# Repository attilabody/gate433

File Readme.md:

# Shared parking space access controller

## Features

Gate433 uses cheap, standard (and insecure) gate opener remotes operating on 433 MHz to control entry and exit of vehicles allowed to acces the parking area.

Each gate opener supposed to be assigned to one vehicle and has unique code. The main purpose of it is to make unfair usage of the parking as inconvinient as possible using commodity gate opener remotes.

Features list:

* 1024 possible remote codes
* Position of each vehicle (inside, outside, unknown) is remembered. Gate opening will be denied for unexpected movements (e.g vehicle which is already inside tries to enter again)
* Access time limits by direction can be set independently for any vehicle (e.g can enter Monday to Friday from 08:30 to 17:00, can leave Monday to Friday from 08:30 to 17:30)
* Vehicle database snd device configuration stored in EEPROM
* Log stored on SD card
* Database changes can be imported from SD card
* Exceptional days (e.g. National holydays) database on SD card
* Automatic DST handling
* Simple command line interpreter on serial for database manipulation, date/time setting, log manipulation and temperature query

## Hardware

There are two versions of the hardware: Original version used Arduino Nano as central component. It is obsoleted by the newer version based on a popular STM32F103C8T6 based minimal board widely known as BluePill. It's actually cheaper on eBay or Aliexpress than the total cost of the components it contains.

Both versions ar using two inputs (usually coming from inductive loop detectors) in addition to the RF signal to decide if a vehicke intends to enter or exit. A pair of tricolor traffic lights provide feedback for drivers.

Both versions have 6 opto-isolated open drain output for 12V LED traffic lights,one opto-isolated open collector output for gate opening and two opto-isolated input for inductive loop detectors.

Second iteration have three extra features compared to the first:

* WiFi to serial bridge for wireless communication
* Rotary encoder driven simpe user interface (yet to be implemented in the firmware)
* 3D printable case modelled in FreeCAD

Prototype of STM32 based version

## Firmware

Arduino Nano based firware was built on Arduino framework using Sloeber Arduino IDE. Source files persist in folders named "gatekeeper", "common" and "libs".  
STM32 version is completely separated as it is based on STM32Cube framework. STM32 sources are placed in "gatekeeper-stm32" and "stm32goodies" folder.

## Schematics and PCB

Arduino based first version hardware developed using proprietrary Eagle free version, and obsoleted by STM32 version but schematics of the [mainboard](docs/V1_mainboard.pdf) and the [IO panel](docs/V1_extio.pdf) are still available for reference.

As mentioned above, hardware of STM32 version designed using KiCAD. The complete EDA project is available in the hardware/STM32 folder. Here are the [schematics](docs/bluepill.pdf) in PDF for easier access.

PCB design for STM32 bsed version

Assembled STM32 panel with modules installed

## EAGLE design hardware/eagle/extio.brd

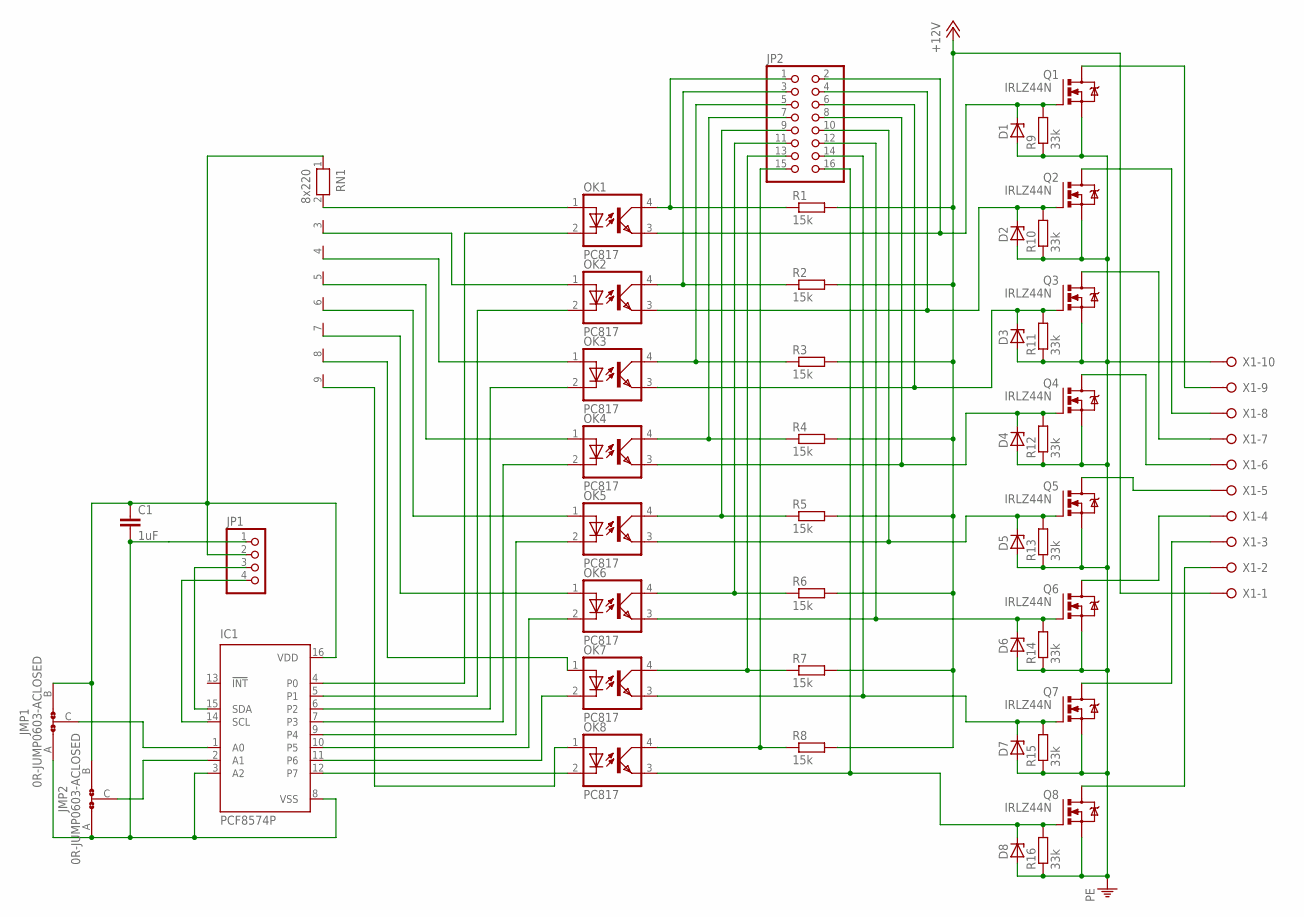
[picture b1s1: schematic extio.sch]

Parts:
C1: 1uF; C0603
D1, D2, D3, D4, D5, D6, D7, D8: ZENER-DIODESOD80C; SOD80C
IC1: PCF8574P; DIL16
JMP1, JMP2: 0R-JUMP0603-ACLOSED; JMP0603-ACLOSED
JP1: PINHD-1X4; 1X04
JP2: PINHD-2X8; 2X08
OK1, OK2, OK3, OK4, OK5, OK6, OK7, OK8: PC817; DIL04
Q1, Q2, Q3, Q4, Q5, Q6, Q7, Q8: IRLZ44N; TO220V
R1, R2, R3, R4, R5, R6, R7, R8: 15k; R0603
R9, R10, R11, R12, R13, R14, R15, R16: 33k; R0603
RN1: 8x220; RN-9
X1: W237-10P

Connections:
+12V: R1.2, R2.2, R3.2, R4.2, R5.2, R6.2, R7.2, R8.2, X1.1
GND: C1.2, IC1.3 (A2), IC1.8 (VSS), JMP1.A, JMP2.A, JP1.1
unnamed: IC1.1 (A0), JMP1.C
unnamed: IC1.2 (A1), JMP2.C
unnamed: OK1.1 (A), RN1.2
unnamed: Q1.2 (D), X1.9
unnamed: JP2.1, OK1.4 (COL), R1.1
unnamed: JP2.3, OK2.4 (COL), R2.1
unnamed: JP2.5, OK3.4 (COL), R3.1
unnamed: JP2.7, OK4.4 (COL), R4.1
unnamed: JP2.9, OK5.4 (COL), R5.1
unnamed: JP2.11, OK6.4 (COL), R6.1
unnamed: JP2.13, OK7.4 (COL), R7.1
unnamed: IC1.12 (P7), OK8.2 (C)
unnamed: IC1.11 (P6), OK7.2 (C)
unnamed: IC1.10 (P5), OK6.2 (C)
unnamed: IC1.9 (P4), OK5.2 (C)
unnamed: IC1.7 (P3), OK4.2 (C)
unnamed: IC1.6 (P2), OK3.2 (C)
unnamed: IC1.5 (P1), OK2.2 (C)
unnamed: IC1.4 (P0), OK1.2 (C)
unnamed: OK2.1 (A), RN1.3
unnamed: OK3.1 (A), RN1.4
unnamed: OK4.1 (A), RN1.5
unnamed: OK5.1 (A), RN1.6
unnamed: OK6.1 (A), RN1.7
unnamed: OK7.1 (A), RN1.8
unnamed: OK8.1 (A), RN1.9
unnamed: D1.C, JP2.2, OK1.3 (EMIT), Q1.1 (G), R9.2
unnamed: IC1.15 (SDA), JP1.3
unnamed: JP2.15, OK8.4 (COL), R8.1
unnamed: D2.C, JP2.4, OK2.3 (EMIT), Q2.1 (G), R10.2
unnamed: D3.C, JP2.6, OK3.3 (EMIT), Q3.1 (G), R11.2
unnamed: D4.C, JP2.8, OK4.3 (EMIT), Q4.1 (G), R12.2
unnamed: D5.C, JP2.10, OK5.3 (EMIT), Q5.1 (G), R13.2
unnamed: D6.C, JP2.12, OK6.3 (EMIT), Q6.1 (G), R14.2
unnamed: IC1.14 (SCL), JP1.4
unnamed: D7.C, JP2.14, OK7.3 (EMIT), Q7.1 (G), R15.2
unnamed: D8.C, JP2.16, OK8.3 (EMIT), Q8.1 (G), R16.2
unnamed: Q2.2 (D), X1.8
unnamed: C1.1, IC1.16 (VDD), JMP1.B, JMP2.B, JP1.2, RN1.1
unnamed: Q3.2 (D), X1.7
unnamed: Q4.2 (D), X1.6
unnamed: Q5.2 (D), X1.5
unnamed: Q6.2 (D), X1.4
unnamed: Q7.2 (D), X1.3
unnamed: Q8.2 (D), X1.2
PE: D1.A, D2.A, D3.A, D4.A, D5.A, D6.A, D7.A, D8.A, Q1.3 (S), Q2.3 (S), Q3.3 (S), Q4.3 (S), Q5.3 (S), Q6.3 (S), Q7.3 (S), Q8.3 (S), R9.1, R10.1, R11.1, R12.1, R13.1, R14.1, R15.1, R16.1, X1.10

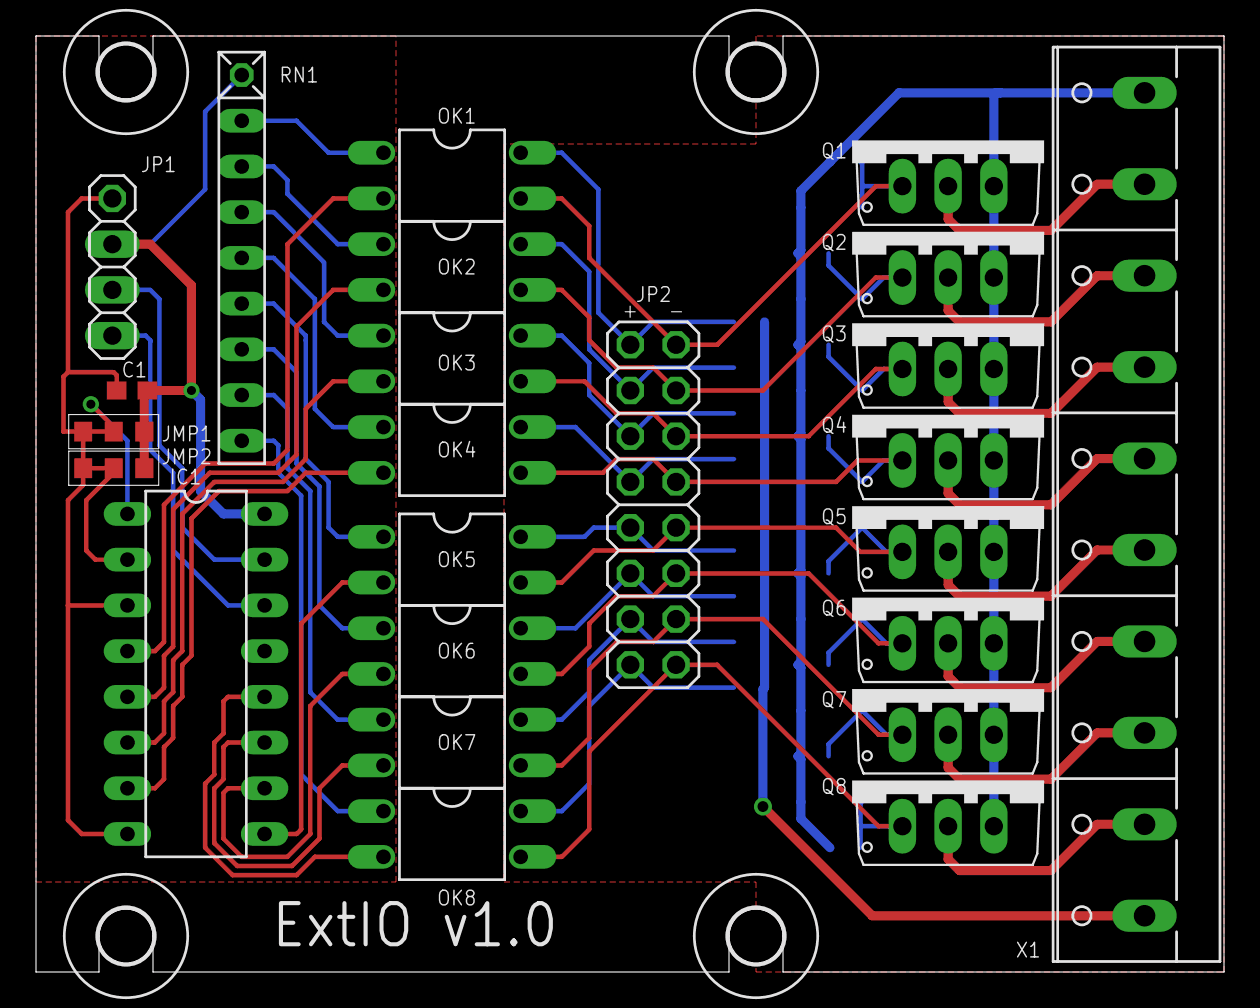
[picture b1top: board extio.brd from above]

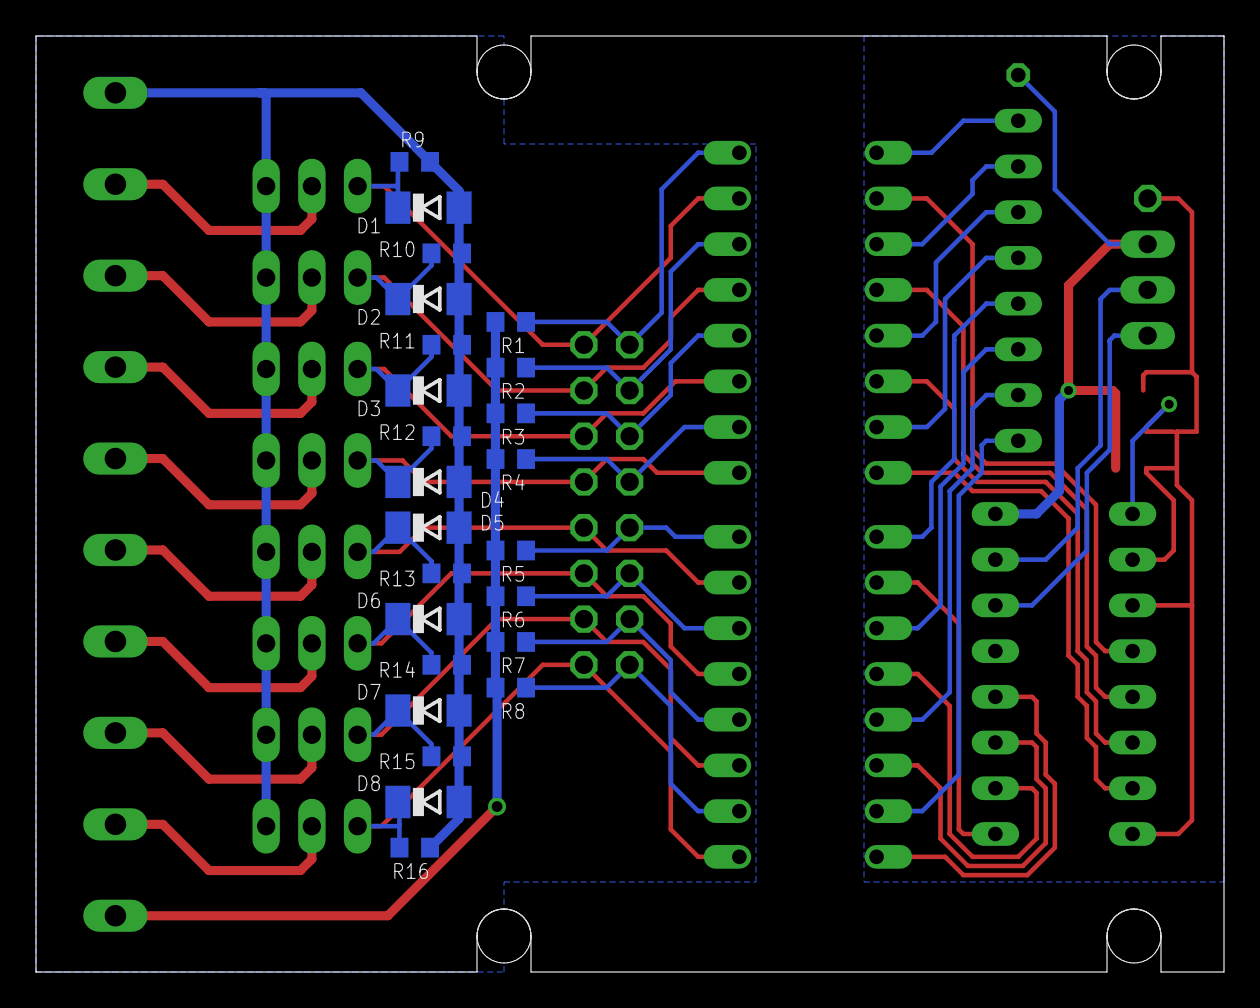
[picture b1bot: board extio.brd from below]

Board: 2 copper layers, 66.0 x 52.0 mm, 52 parts (24 on the bottom side), 48 nets.

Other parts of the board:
U$1, U$2, U$3, U$4: 3,0

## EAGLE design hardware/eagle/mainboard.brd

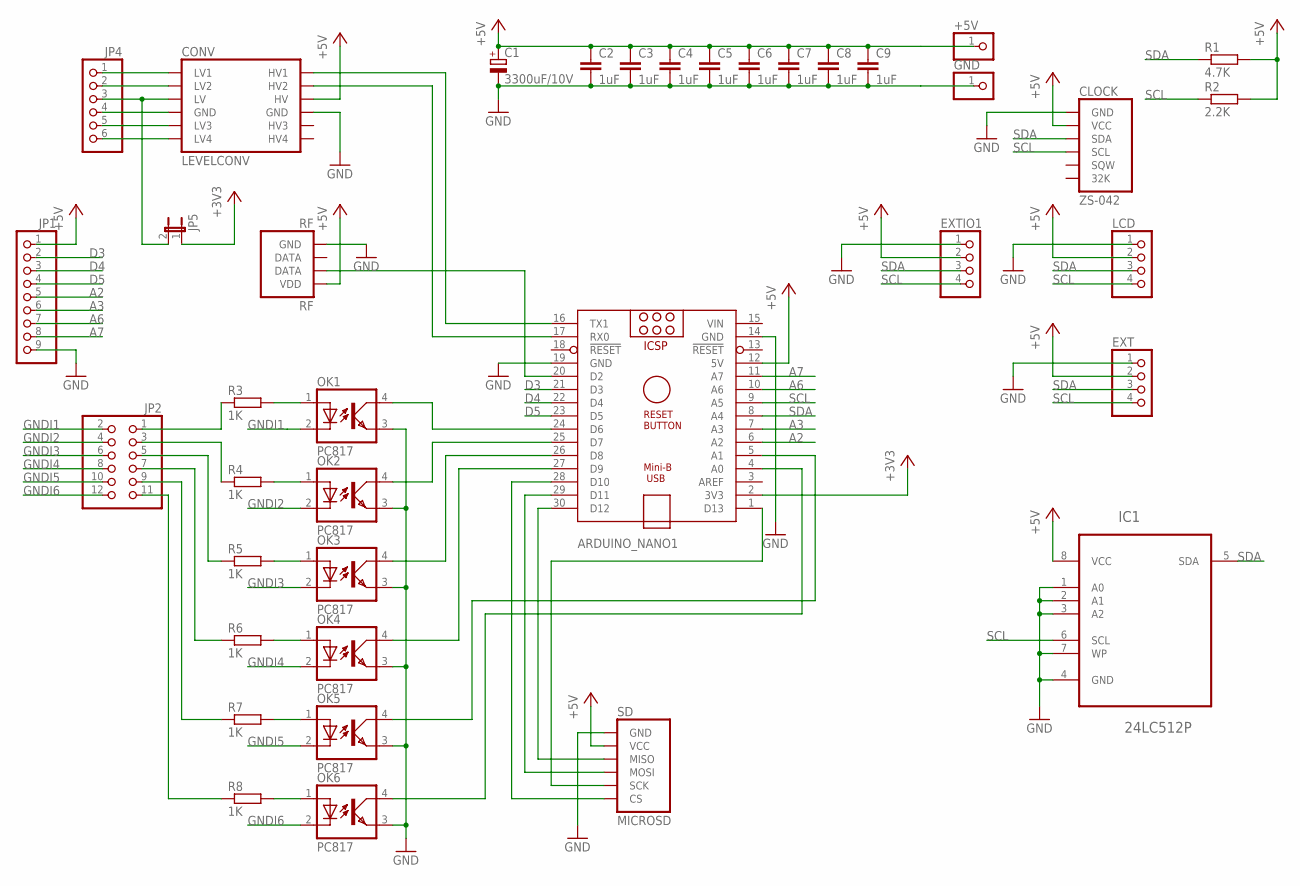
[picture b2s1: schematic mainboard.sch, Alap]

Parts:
+5V: PINHD-1X1; 1X01
ARDUINO_NANO1: ARDUINO_NANO
C1: 3300uF/10V; E5-10,5
C2, C3, C4, C5, C6, C7, C8, C9: 1uF; C0603
CLOCK: ZS-042
CONV: LEVELCONV
EXT: PINHD-1X4; 1X04
EXTIO1: PINHD-1X4; 1X04
GND: PINHD-1X1; 1X01
IC1: 24LC512P; DIP254P762X533-8
JP1: PINHD-1X9; 1X09
JP2: PINHD-2X6; 2X06
JP4: PINHD-1X6; 1X06
JP5: JP1E; JP1
LCD: PINHD-1X4; 1X04
OK1, OK2, OK3, OK4, OK5, OK6: PC817; DIL04
R1: 4.7K; R0603
R2: 2.2K; R0603
R3, R4, R5, R6, R7, R8: 1K; R0603
RF: RF
SD: MICROSD

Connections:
+3V3: ARDUINO_NANO1.2 (3V3), JP5.1
+5V: +5V.1, ARDUINO_NANO1.12 (5V), C1.+, C2.1, C3.1, C4.1, C5.1, C6.1, C7.1, C8.1, C9.1, CLOCK.2 (VCC), CONV.10 (HV), EXT.2, EXTIO1.2, IC1.8 (VCC), JP1.1, LCD.2, R1.2, R2.2, RF.4 (VDD), SD.2 (VCC)
A2: ARDUINO_NANO1.6 (A2), JP1.5
A3: ARDUINO_NANO1.7 (A3), JP1.6
A6: ARDUINO_NANO1.10 (A6), JP1.7
A7: ARDUINO_NANO1.11 (A7), JP1.8
D3: ARDUINO_NANO1.21 (D3), JP1.2
D4: ARDUINO_NANO1.22 (D4), JP1.3
D5: ARDUINO_NANO1.23 (D5), JP1.4
GND: ARDUINO_NANO1.14 (GND), ARDUINO_NANO1.19 (GND), C1.-, C2.2, C3.2, C4.2, C5.2, C6.2, C7.2, C8.2, C9.2, CLOCK.1 (GND), CONV.9 (GND), EXT.1, EXTIO1.1, GND.1, IC1.1 (A0), IC1.2 (A1), IC1.3 (A2), IC1.4 (GND), IC1.7 (WP), JP1.9, LCD.1, OK1.3 (EMIT), OK2.3 (EMIT), OK3.3 (EMIT), OK4.3 (EMIT), OK5.3 (EMIT), OK6.3 (EMIT), RF.1 (GND), SD.1 (GND)
GNDI1: JP2.2, OK1.2 (C)
GNDI2: JP2.4, OK2.2 (C)
GNDI3: JP2.6, OK3.2 (C)
GNDI4: JP2.8, OK4.2 (C)
GNDI5: JP2.10, OK5.2 (C)
GNDI6: JP2.12, OK6.2 (C)
unnamed: CONV.1 (LV1), JP4.1
unnamed: JP2.11, R8.1
unnamed: OK1.1 (A), R3.2
unnamed: ARDUINO_NANO1.27 (D9), OK4.4 (COL)
unnamed: ARDUINO_NANO1.26 (D8), OK3.4 (COL)
unnamed: ARDUINO_NANO1.25 (D7), OK2.4 (COL)
unnamed: JP2.9, R7.1
unnamed: CONV.2 (LV2), JP4.2
unnamed: CONV.3 (LV), JP4.3, JP5.2
unnamed: CONV.5 (LV3), JP4.5
unnamed: CONV.6 (LV4), JP4.6
unnamed: CONV.4 (GND), JP4.4
unnamed: ARDUINO_NANO1.28 (D10), SD.6 (CS)
unnamed: ARDUINO_NANO1.1 (D13), SD.5 (SCK)
unnamed: ARDUINO_NANO1.29 (D11), SD.4 (MOSI)
unnamed: ARDUINO_NANO1.30 (D12), SD.3 (MISO)
unnamed: ARDUINO_NANO1.24 (D6), OK1.4 (COL)
unnamed: JP2.1, R3.1
unnamed: JP2.3, R4.1
unnamed: ARDUINO_NANO1.4 (A0), OK6.4 (COL)
unnamed: ARDUINO_NANO1.5 (A1), OK5.4 (COL)
unnamed: ARDUINO_NANO1.20 (D2), RF.3 (DATA)
unnamed: JP2.5, R5.1
unnamed: JP2.7, R6.1
unnamed: OK2.1 (A), R4.2
unnamed: OK3.1 (A), R5.2
unnamed: OK4.1 (A), R6.2
unnamed: OK5.1 (A), R7.2
unnamed: OK6.1 (A), R8.2
unnamed: ARDUINO_NANO1.16 (TX1), CONV.12 (HV1)
unnamed: ARDUINO_NANO1.17 (RX0), CONV.11 (HV2)
SCL: ARDUINO_NANO1.9 (A5), CLOCK.4 (SCL), EXT.4, EXTIO1.4, IC1.6 (SCL), LCD.4, R2.1
SDA: ARDUINO_NANO1.8 (A4), CLOCK.3 (SDA), EXT.3, EXTIO1.3, IC1.5 (SDA), LCD.3, R1.1
VIN: ARDUINO_NANO1.15 (VIN)

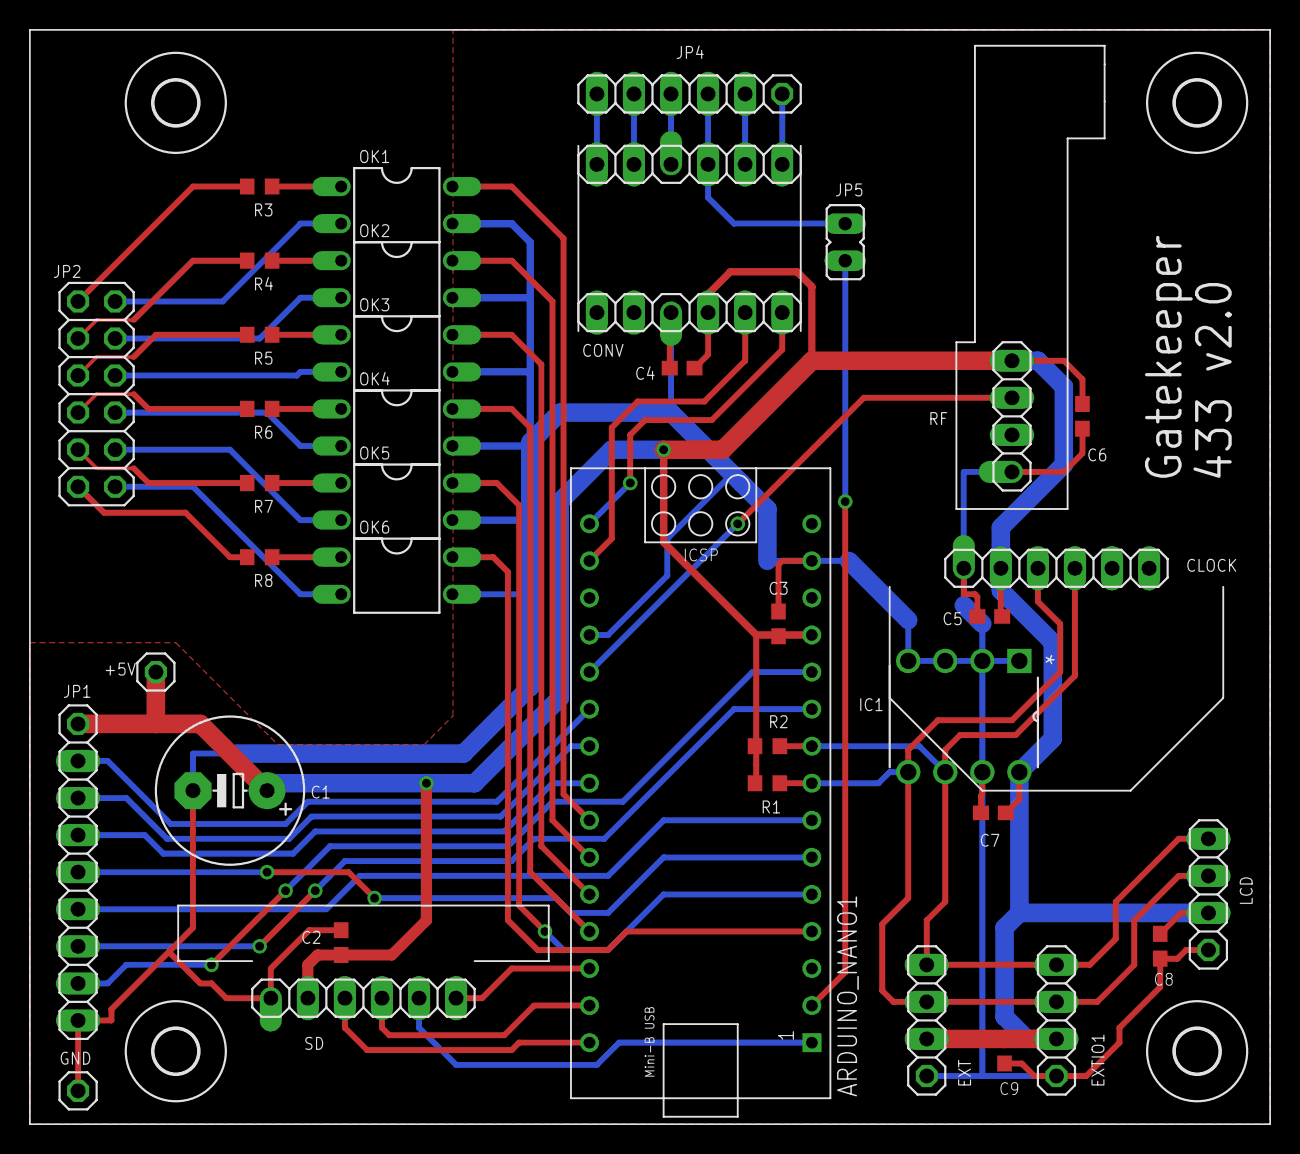
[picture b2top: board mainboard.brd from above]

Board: 2 copper layers, 85.0 x 75.0 mm, 42 parts (0 on the bottom side), 49 nets.

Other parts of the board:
U$1, U$2, U$3, U$4: 3,0

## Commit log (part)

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2015-09-27 interrupt driven listing
2015-09-29 Using timer0 compare a interrupt to afterglow LED
2015-10-03 globals
2015-10-03 Squashed 'libs/Time/' content from commit a7cc326
    git-subtree-dir: libs/Time
    git-subtree-split: a7cc3261f91af37ca3d8c8e192fa4030445178e7
2015-10-05 gatedemo_test created
2015-10-05 timing.txt added
2015-10-06 faking
2015-10-06 VS test session fixes
2015-10-07 ignoring *.d
2015-10-07 corrected high/low drive
2015-10-07 variable rename (curmicro->now)
2015-10-09 using local static variable tor data shifting to improve locking in ISR
2015-10-10 tuning
2015-10-10 stats
2015-10-11 cleaning up && fixing timing
2015-10-14 Squashed 'libs/ds3231/' content from commit 9ea45be
    git-subtree-dir: libs/ds3231
    git-subtree-split: 9ea45be66f0b5374a520a9630fde649175f5f068
2015-10-15 ds3231 progress
2015-10-16 Squashed 'libs/Adafruit-GFX-Library/' content from commit 0acee33
    git-subtree-dir: libs/Adafruit-GFX-Library
    git-subtree-split: 0acee33cfe8b500c5a2a1c4f29913746936b53ba
2015-10-16 Squashed 'libs/TFTLCDplus-Library/' content from commit 82b13b3
    git-subtree-dir: libs/TFTLCDplus-Library
    git-subtree-split: 82b13b39e15d263f9cafa06388a885511f3b6400
2015-10-17 DS3231
2015-10-17 renaming madness
2015-10-17 demo
2015-10-18 making it compile again (step 1)
2015-10-21 getintparam bugfix
2015-10-22 GET SET SETF SHOW implemented
2015-10-24 buttons
2015-10-25 refactor for displaying communication
2015-10-27 moving repetition limit from loop() to ISR, explicitly sized types ((u)int_#_t)
2015-10-28 BAUDRATE TO 38400
2015-10-29 renamint interface.cpp to interface_main.cpp
2015-10-29 gatehandler beginnings + common interface code
2015-10-30 common functions moved out
2015-10-30 testing 1,2,3
2015-10-31 remote recording ready.
2015-11-01 getintparam cleanup, dbrecord parsing
2015-11-03 test fixed to debug brain demaged remote control fix
2015-11-06 changing types (to explicitly sized)
2015-11-08 separated info & status file step 1
2015-11-08 separated info & status file step 2
2015-11-09 command parsing bugfix
2015-11-09 excluding lib examples
2015-11-12 gatelogic: database handler class proto
2015-11-12 gatelogic: database handler progress
2015-11-13 gatelogic_test
2015-11-15 fakelibs reorg
2015-11-17 gatelogic progress
2015-11-27 boardtest added
2015-12-06 merging subtreerepos.txt content from gatelogic
2015-12-09 inductiveloop progress (get rid of config.h dependency)
2015-12-09 LiquidCrystal_I2C library added
2015-12-10 common added to boardtest
2015-12-10 boardtest working
2015-12-12 boardtest set time
2015-12-13 database related stuff moved to common
2015-12-14 making gatelogic_test to compile
2015-12-17 boardtest: component ifdefs
2015-12-18 added executeable permission to python scripts
2015-12-18 RF signal decoding parts moved to common
2015-12-18 lamp class seems to be working
2015-12-19 removing some debris
2015-12-21 inductiveloop tuning
2015-12-23 failstats to decode433
2015-12-29 assembling
2015-12-30 trafficlights_test: LCD
2015-12-31 trafficlights_test: code from serial
2016-01-01 trafficlights_test: testing && fixing session results
2016-01-01 project renames gatelogic -> gatekeeper trafficlights_test -> testbed
2016-01-01 testbed progress (set serial command)
2016-01-03 boardtest compile fix && remove trafficlights testing
2016-01-03 very WIP
2016-01-04 thindb
2016-01-05 LCD bug (constructor &) fixed.
2016-01-05 using PCF8574 instead of arduino I/O pins for relay output
2016-01-06 hybriddb first checkin (expect shore edges)
2016-01-07 added streaming library to libs
2016-01-08 i2c_eeprom class
2016-01-09 flashdb fixing
2016-01-10 minor boardtest improvements
2016-01-11 minor boardtst improvements
2016-01-11 gatelogic.cpp renamed to gatekeeper
2016-01-18 gatelogic_test renamed to gatekeeper_test
2016-01-21 relaxed mode (for "beta")
2016-01-24 testbed compile fix
2016-01-27 date exception handling
2016-01-27 testbed reorg
2016-01-27 logging v2
2016-01-28 boardtest lcd reorg
2016-01-29 GOD mode (emergency) code handling
2016-01-30 trafficlights instance moved into gatehandler (was global)
2016-01-30 gate relay handled by outputpin class eliminate m_[hig|low]value from outputpin
2016-01-31 gatekeeper log filling on receive bugfix
2016-02-02 importdb (creates simpledb file form owners.txt and tenants.txt)
2016-02-02 boardtest print free memory to LCD at startup
2016-02-02 preparing relay output gpio abstraction
2016-02-02 gatekeeper: cs command (clean ststuses)
2016-02-04 refactoring decoder code handling
2016-02-04 hybintdb (SD+internal eeprom) gatekeeper: additiona logging before and after DB update
2016-02-12 log dump watchdog update
2016-02-13 Squashed 'libs/TimerOne/' content from commit 9790739
    git-subtree-dir: libs/TimerOne
    git-subtree-split: 979073973b09aa5d084224fe351e7b46ed358f6e
2016-02-13 gk_simple: logging
2016-02-13 loadtest: initial commit
2016-02-13 gk_simple: ID should be between 4 and 1019
2016-02-13 gk_simple: handle lights
2016-02-13 gk_simple
2016-02-13 gk_simple: added valid date/time to log
2016-02-13 gk_simple: Fixing traffic lights pins (inside<->outside)
2016-02-13 codereader: prettier print
2016-02-13 gk_simple: VERBOSE
2016-02-13 codereader: initial commit
2016-02-13 codereader: adding SD log
2016-02-13 boardtest: reverse 433 decoding switched on
2016-02-13 libs/I2C: added write16 and read16 functions
2016-02-14 syncing to markers (gate433 related)
2016-02-15 coredeader: USE_SDCARD && dummylogwriter
2016-02-16 codereader: RTC handling
2016-02-16 common: decode433 tuning
2016-02-17 gk_simple using libs/I2C
    ds3231 using libs/I2C
2016-02-17 boardtest: stress testintg I2C; switch off reversed RF bit order gatekeeper: switch off reversed RF bit order
2016-02-17 libs/I2C: write16 bugfix
2016-02-18 libs/PCF8574: Wire->I2c testbed: i2cioexttest
2016-02-18 boardtest: using new I2C lib based devices
2016-02-18 gk_simple: db import (to EEPROM)
2016-02-21 boardtest: incoming code logging
2016-02-27 gk_simple: remote controller registration restrictions effective.
2016-03-01 gk_simple: inductive loop aborts traffic light delay
2016-03-05 gatekeeper: + I2C lib; + gatehandler invalid state protection; codereader: Enable I2C lib loadtest: include path fix (+common)
2016-03-06 createdb: gitignore case issue fix
2016-03-13 gk_simple: Switching green to red when induction loop changes during passage, holding it until there's no car on either loops.
2016-03-15 * optimization; + updateloopstatuscalc
2016-03-17 gk_simple: eepromdb -> i2cdb
2016-03-18 loadtest: rf code sending (send, sweep commands)
2016-03-23 importdb fix and optimalization
2016-03-23 DS3231Test
2016-03-25 * DS3231 full static class + DST capability moved to DS3231_DST + class DS3231 function calls replaced to DS3231_DST calls * gk_simple EEPROM.h fix
2016-03-27 gatekeeper: datetime update over-optimization bug fix
2016-03-28 libs/DS3231: manual-optimizing get & set for size boardtest: use DS3231 class for date&time
2016-03-28 + auto wday in DS3231; - parsedatetime wday;
2016-04-01 + decode433 stop watch (>last cycle time) after 12 bit
2016-04-02 Eclipse Arduino plugin V3 conversion
2016-04-03 loadtest: Build fix (project settings)
2016-04-05 createdb: - backing up DB.TXT (to DB.BAK) on import - ignoring backup files in git
2016-04-08 gatekeeper: - trafficlights is a global now (as loop, db, etc) - switching on and off lights at restart - time invalid status appears on the display
2016-04-09 gatekeeper: moved output classes to common
2016-04-14 GPIO: detaching outputpin from g_outputs (prepare moving of gate open signal to a different output port)
2016-04-14 libs/i2c_eeprom: I2C error handling
2016-04-17 barereader: decode433 (from common) added
2016-04-17 barereader: LED eye-candy common/decode433: counting overruns (up to 255)
2016-04-21 freqcntr: first functional version
2016-04-22 gatekeeper: re-think WARN
2016-04-29 Eclipse blah
2016-05-14 freqcntr: I2C LCD feature switch
2016-06-05 hardware: schematics and board added
2016-06-06 extio board
2016-06-08 mainboard SMD update
2016-06-08 extio connector fix
2016-06-11 extio C1 to SMD
2016-06-12 kicad-ioext: wiring
2016-06-12 hardware: eagle files moved from hardware/ to hardware/eagle/ kicad files moved from kicad/ to harware/kicad/ .gitignore modified to follow changes
2016-06-16 ExtIO A0..A1: jmp1..jmp2
2016-06-19 hardware/kicad ioext: use 3x jumper block insterad of inidividual jumpers
2016-07-16 gatekeeper: CLR by SD
2016-07-24 gatekeeper: enable watchdog timer (!!!uno bootloader required!!!) ddb && dl: data lines start with ">" instead of ":" log dump: additional parameter to truncate after dump
2017-05-11 Logger Auth messages fix for missing btn parameter
2017-05-11 eclipse preferences
2017-06-07 gatekeeper converted to sloeber 4.1 IDE
2018-01-11 bluepill: basic timer setup for semaphore outputs
2018-01-13 bluepill: timer interrupts for RF activated
2018-01-13 bluepill: Added RF decoder skeleton
2018-01-13 bluepill: Added stm32goodies to the project
2018-01-14 bluepill: Singleton<> moved to st32goodies
2018-01-15 bluepill: RF decoder working
2018-01-16 bluepill: RFDecoder: moved interrupt enablement to a separate Init() to avoid singleton initialization problem (get rid of SafeSingletonInitializer<> usage).
2018-01-16 bluepill: added SPI SD BSP and demo code
2018-01-18 DbgUsart stream operators
2018-01-18 hardware/stm32: bluepill schematics && PCB progress
2018-01-18 bluepill: Added SdFile, Loop detector inputs, USART3 for ESP-01
2018-01-19 bluepill: PCB 0.9
2018-01-20 bluepill PCB: SD Card socket turned around
2018-01-23 I2cEEPROM
2018-01-27 I2cMaster functions epect void* buffer pointers
2018-01-27 DS3231 added
2018-01-27 DbgUsart supports receiving
2018-02-01 All hardware handlers are working
2018-02-04 gate433-stm32: database and i2cdb ported from atmel version pwmoutputs and smartlights are working MainLoop class introduced
2018-02-05 Added license for STM32 hardware
2018-02-08 Usart: Renamed to Usart from DbgUsart Passing references to interfaces instead of pointers Usart is no singleton anymore (to allow multiple instances) Init() eliminated Using char* for buffers instea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
2018-02-08 strutil: Typo fix & resolve char signedness issue in getintparam()
2018-02-08 i2ceeprom: NeedPoll() bugfix
2018-02-08 SDFile: Open mode enum refactor, Size() implementation
2018-02-08 gate433-stm32: ITick.h->tick.h rename
2018-02-08 gate433-stm32: serial command line processing
2018-02-08 gate433-stm32: rename files to lowercase
2018-02-13 gate433-stm32: SD log writer added
2018-02-13 gate433-stm32: incoming codes are logged to SD SD log can be dumped to serial
2018-02-20 strutil: scalar to string function will render exact count of digits ds3231: number of year digits can be passed for date to string conversion
2018-02-20 gate433-stm32: almost there (need to implement Mainloop::Authorize)
2018-02-27 usart: functions returning numbers of characters sent now return size_t
2018-03-03 eliminating warnings (missing virtual destructor)
2018-03-03 gate433-stm32: UART: UART1 speed back to 115200, UART3 activated and handled the same as UART1 Timer initialization in main.c to shorten full power period for all lights on boot gt (Get Temperature) 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
2018-03-07 stm32 board test: added stm32goodies
2018-03-08 bluepill commandprocessor: new logic to handle renge for CS, handlers commented (function) sdlogwriter: const correctness, log queue mainloop: log if usart::Receive fails, log queue support
2018-03-10 bluepill: Opening and closing the gate
2018-03-16 Bluepill: Change rotary encoder button line to EXTI Decrease interrupt priority of everything except I2C
2018-03-17 i2clcd: removed inline from private finctions, added one char Print
2018-03-17 Bluepill: SHUFFLE.TXT handling
2018-03-18 File name CamelCasing
2018-03-18 bluepill: followup for Stm32Goodues changes (file/function renames)
2018-03-25 bluepill: transit timeout fix
2018-04-16 Added FreeCAD model of the case for STM32 version
2018-04-17 Config stuff
2018-04-17 More descriptive command names
2018-04-18 bluepill: Getting rid of designated initializers which will be standardized only in c++20
